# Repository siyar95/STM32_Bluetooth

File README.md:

# STM32_Bluetooth

A compact STM32WB55CEU6-based Bluetooth module designed for embedded wireless applications. This board features a u.FL antenna connector, USB-C interface, and UART communication — making it ideal for low-power wireless development and integration.

---

## 🔧 Features

- **Microcontroller**: STM32WB55CEU6 (Bluetooth 5.2 + Cortex-M4 + Cortex-M0+)
- **Bluetooth Antenna**: u.FL connector for external antenna
- **USB Interface**: USB-C for power and data
- **Communication**: UART breakout for serial interfacing
- **Power Supply**: 5V USBC --> 3.3V LDO regulator --> 1.2V SMPS (in the MCU) for efficient power conversion
- **Oscillators**:
  - 32 MHz HSE (for Bluetooth stack)
  - 32.768 kHz LSE (for RTC and low-power modes)

---

## 🧱 PCB Stackup (4-layer)

| Layer | Purpose           |
|-------|--------------------|
| L1    | Signal (Top)       |
| L2    | Ground Plane       |
| L3    | Ground Plane       |
| L4    | Power / Signal     |

Optimized for signal integrity, RF performance, and low EMI.

---

## 🧩 Ideal For

- Bluetooth Low Energy (BLE) applications
- Custom wearable or IoT devices
- Prototyping wireless peripherals with STM32Cube ecosystem
- Projects needing UART or USB-C connectivity alongside BLE

---

## 📡 Notes

- Make sure to connect a suitable external antenna via the u.FL connector.
- Crystal oscillator frequencies comply with STM32WB Bluetooth stack requirements.
- USB-C supports both power and USB device functionality.

---

## 🛠️ Tools

- Designed in **KiCad**
- Program using **STM32CubeIDE** or **STM32CubeProgrammer**

## Screenshots

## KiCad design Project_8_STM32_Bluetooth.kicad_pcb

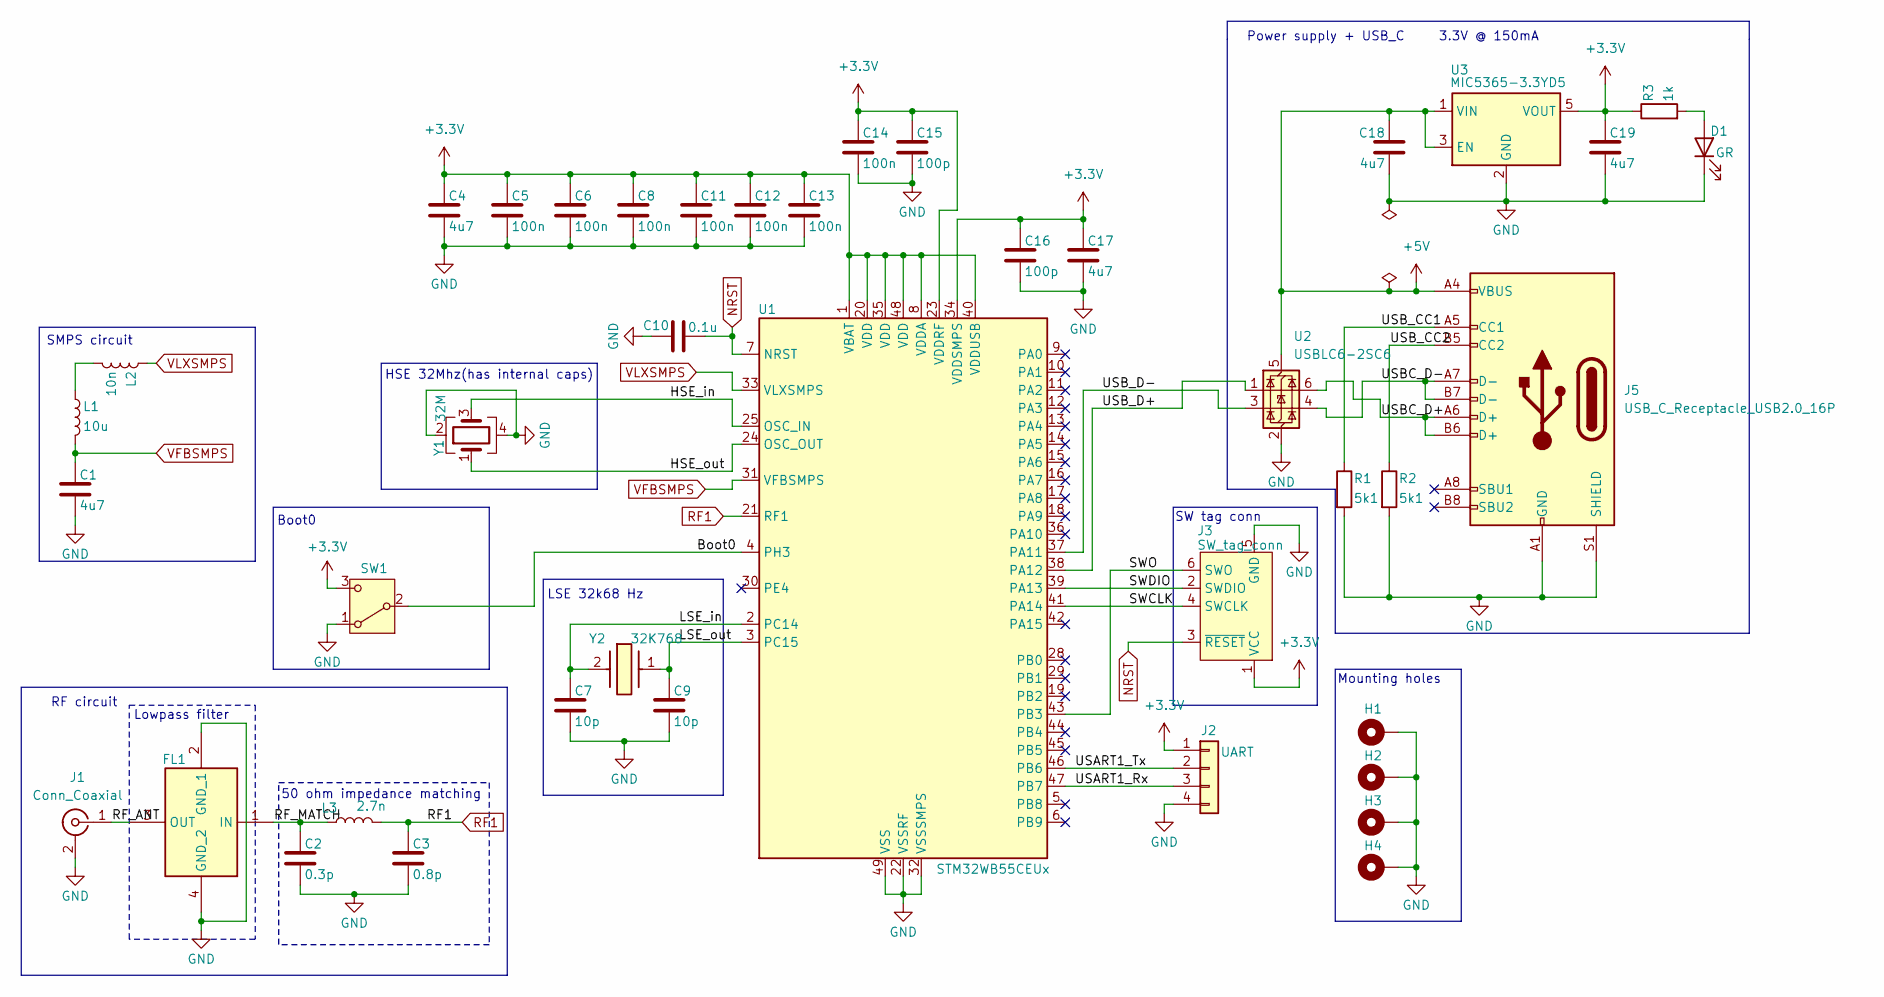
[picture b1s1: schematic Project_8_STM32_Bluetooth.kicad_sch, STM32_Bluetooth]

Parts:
C1, C4, C17: 4u7; C_0402_1005Metric
C2: 0.3p; C_0402_1005Metric
C3: 0.8p; C_0402_1005Metric
C5, C6, C8, C11, C12, C13, C14: 100n; C_0402_1005Metric
C7, C9: 10p; C_0402_1005Metric
C10: 0.1u; C_0402_1005Metric
C15, C16: 100p; C_0402_1005Metric
C18, C19: 4u7; C_0805_2012Metric
D1: GR; LED_0805_2012Metric
FL1: DLF162500LT-5028A1; LPF; Mouser Part Number 810-DLF16250LT5028A1
H1, H2, H3, H4: MountingHole_Pad; MountingHole_2.5mm_Pad_Via
J1: Conn_Coaxial; U.FL_Hirose_U.FL-R-SMT-1_Vertical
J2: UART; PinHeader_1x04_P2.54mm_Vertical
J3: SW_tag_conn; Tag-Connect_TC2030-IDC-FP_2x03_P1.27mm_Vertical
J5: USB_C_Receptacle_USB2.0_16P; USB_C_Receptacle_XKB_U262-16XN-4BVC11
L1: 10u; L_0805_2012Metric
L2: 10n; L_0402_1005Metric
L3: 2.7n; L_0402_1005Metric
R1, R2: 5k1; R_0402_1005Metric
R3: 1k; R_0402_1005Metric
SW1: SW_SPDT; SW_SPDT_PCM12
U1: STM32WB55CEUx; QFN-48-1EP_7x7mm_P0.5mm_EP5.6x5.6mm
U2: USBLC6-2SC6; SOT-23-6
U3: MIC5365-3.3YD5; SOT-23-5
Y1: 32M; Crystal_SMD_2016-4Pin_2.0x1.6mm
Y2: 32K768; NX2012SA32768KSTDMUB1; Mouser Part Number 344-NX2012SA32768K1

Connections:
+3.3V: C4.1, C5.1, C6.1, C8.1, C11.1, C12.1, C13.1, C14.1, C15.1, C16.1, C17.1, C19.1, J2.1, J3.1 (VCC), R3.1, SW1.3 (C), U1.1 (VBAT), U1.8 (VDDA), U1.20 (VDD), U1.23 (VDDRF), U1.34 (VDDSMPS), U1.35 (VDD), U1.40 (VDDUSB), U1.48 (VDD), U3.5 (VOUT)
+5V: C18.1, J5.A4 (VBUS), J5.A9 (VBUS), J5.B4 (VBUS), J5.B9 (VBUS), U2.5 (VBUS), U3.1 (VIN), U3.3 (EN)
/Boot0: SW1.2 (B), U1.4 (PH3)
/HSE_in: U1.25 (OSC_IN), Y1.3
/HSE_out: U1.24 (OSC_OUT), Y1.1
/LSE_in: C7.1, U1.2 (PC14), Y2.2 (CRYSTAL)
/LSE_out: C9.1, U1.3 (PC15), Y2.1 (CRYSTAL)
/RF_ANT: FL1.3 (OUT), J1.1 (In)
/RF_MATCH: C2.1, FL1.1 (IN), L3.1
/SWCLK: J3.4 (SWCLK), U1.41 (PA14)
/SWDIO: J3.2 (SWDIO), U1.39 (PA13)
/SWO: J3.6 (SWO), U1.43 (PB3)
/USART1_Rx: J2.3, U1.47 (PB7)
/USART1_Tx: J2.2, U1.46 (PB6)
/USBC_D+: J5.A6 (D+), J5.B6 (D+), U2.6 (I/O1)
/USBC_D-: J5.A7 (D-), J5.B7 (D-), U2.4 (I/O2)
/USB_CC1: J5.A5 (CC1), R1.1
/USB_CC2: J5.B5 (CC2), R2.1
/USB_D+: U1.38 (PA12), U2.1 (I/O1)
/USB_D-: U1.37 (PA11), U2.3 (I/O2)
GND: C1.2, C2.2, C3.2, C4.2, C5.2, C6.2, C7.2, C8.2, C9.2, C10.2, C11.2, C12.2, C13.2, C14.2, C15.2, C16.2, C17.2, C18.2, C19.2, D1.1 (K), FL1.2 (GND_1), FL1.4 (GND_2), H1.1, H2.1, H3.1, H4.1, J1.2 (Ext), J2.4, J3.5 (GND), J5.A1 (GND), J5.A12 (GND), J5.B1 (GND), J5.B12 (GND), J5.S1 (SHIELD), R1.2, R2.2, SW1.1 (A), U1.22 (VSSRF), U1.32 (VSSSMPS), U1.49 (VSS), U2.2 (GND), U3.2 (GND), Y1.2, Y1.4
NRST: C10.1, J3.3 (~RESET), U1.7 (NRST)
unnamed: D1.2 (A), R3.2
unnamed: L1.1, L2.2
RF1: C3.1, L3.2, U1.21 (RF1)
VFBSMPS: C1.1, L1.2, U1.31 (VFBSMPS)
VLXSMPS: L2.1, U1.33 (VLXSMPS)

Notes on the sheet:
SW tag conn
Boot0
50 ohm impedance matching
Lowpass filter
LSE 32k68 Hz
SMPS circuit
Mounting holes
RF circuit
Power supply + USB_C 3.3V @ 150mA
HSE 32Mhz(has internal caps)

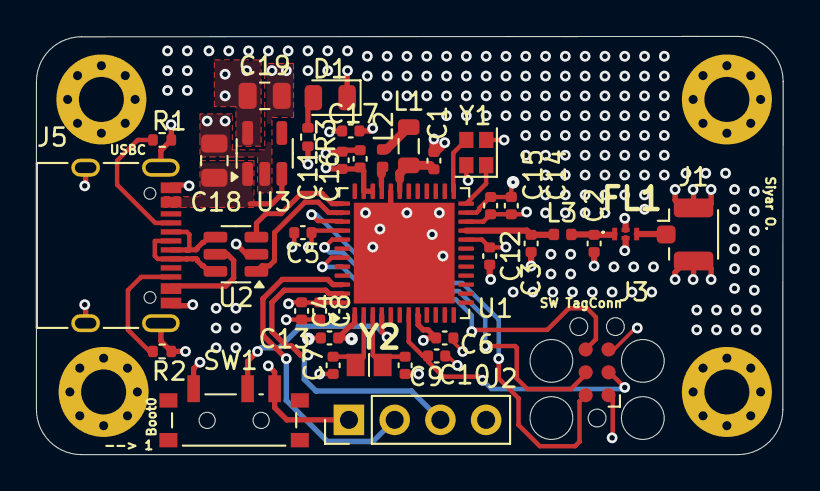
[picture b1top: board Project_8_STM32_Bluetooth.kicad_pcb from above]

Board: 4 copper layers, 41.5 x 23.2 mm, 41 parts (0 on the bottom side), 27 nets.

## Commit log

2025-05-16 Rename Project_8_STM32_Bluetooth.kicad_pro to Hardware/Project_8_STM32_Bluetooth.kicad_pro
